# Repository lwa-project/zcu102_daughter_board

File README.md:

ZCU102 Daughter Board
=====================
This repo contains the build files for the daughter board needed to connect
the LWA digitizers to a ZCU102 dev. board.

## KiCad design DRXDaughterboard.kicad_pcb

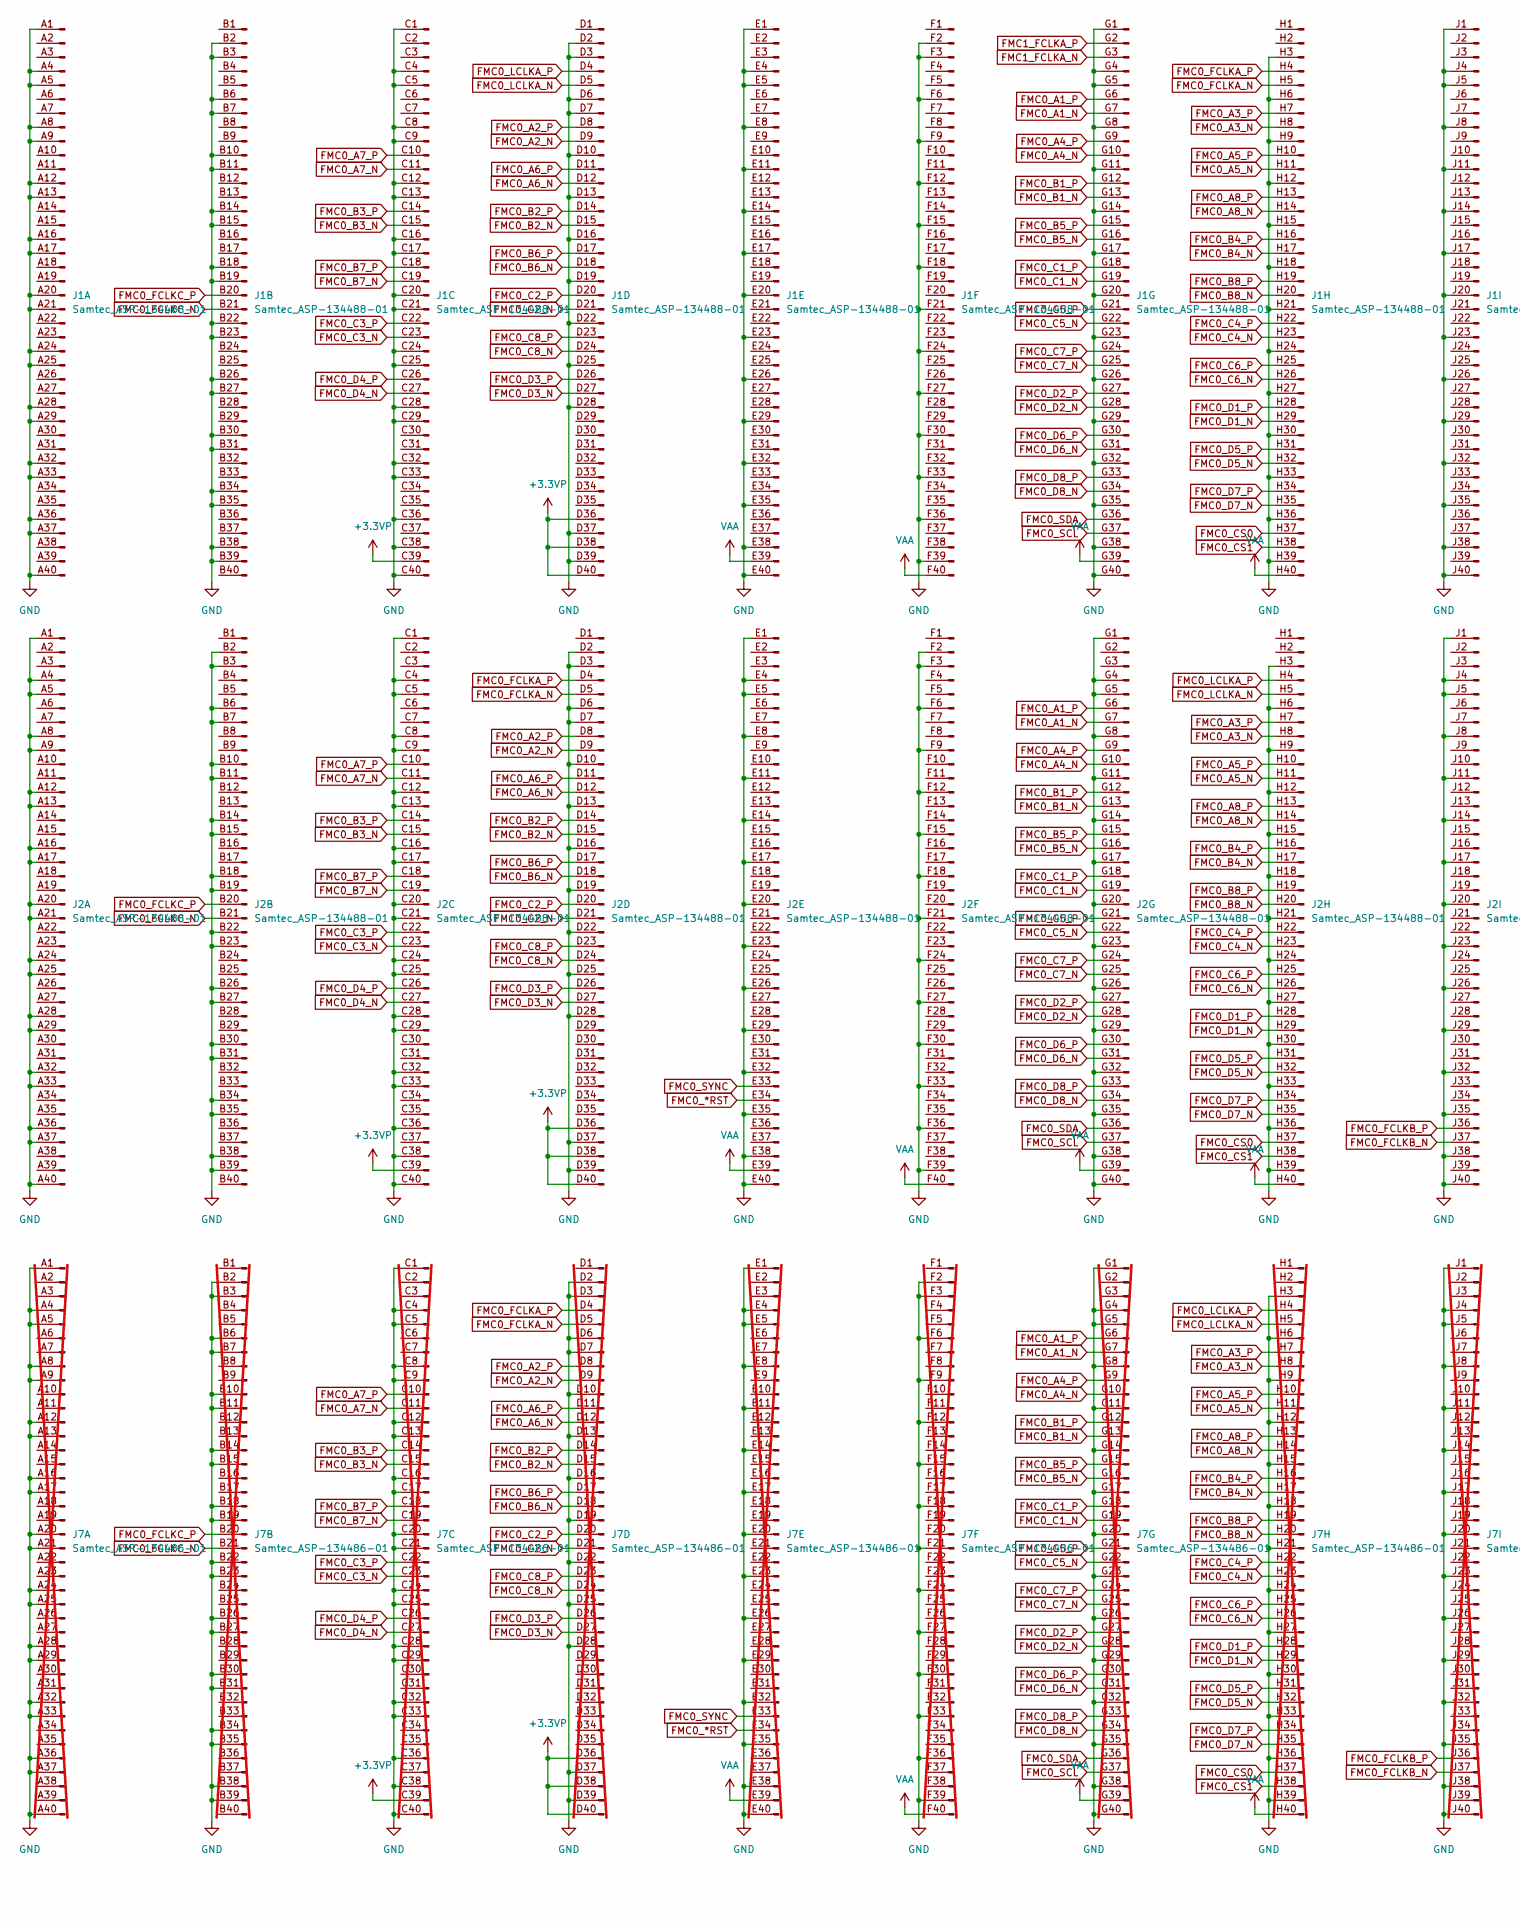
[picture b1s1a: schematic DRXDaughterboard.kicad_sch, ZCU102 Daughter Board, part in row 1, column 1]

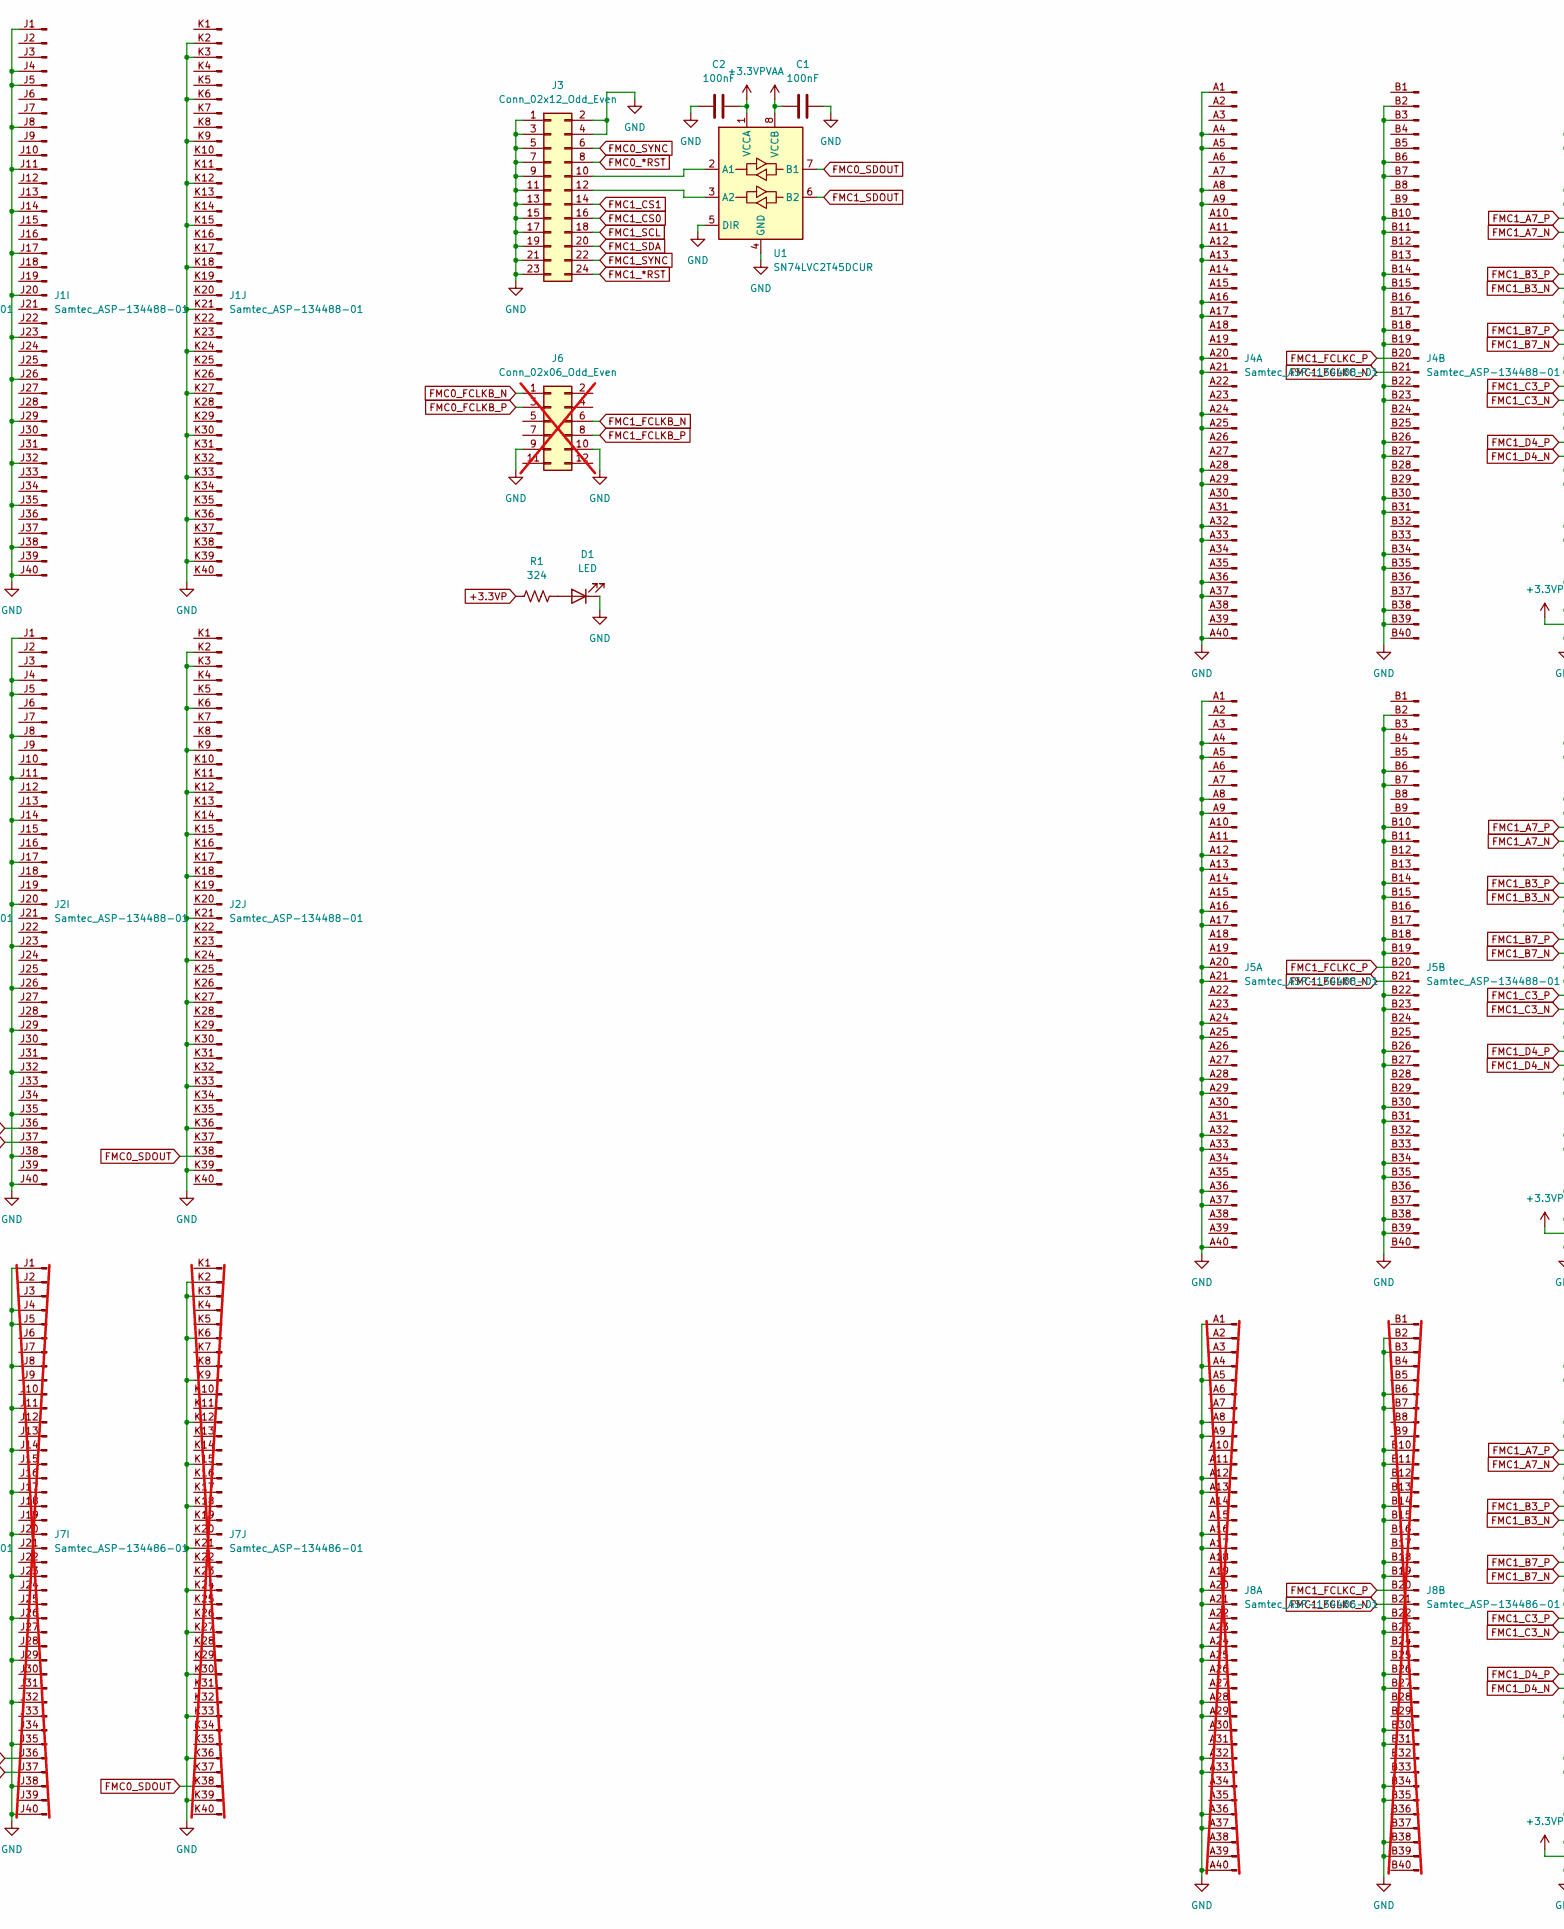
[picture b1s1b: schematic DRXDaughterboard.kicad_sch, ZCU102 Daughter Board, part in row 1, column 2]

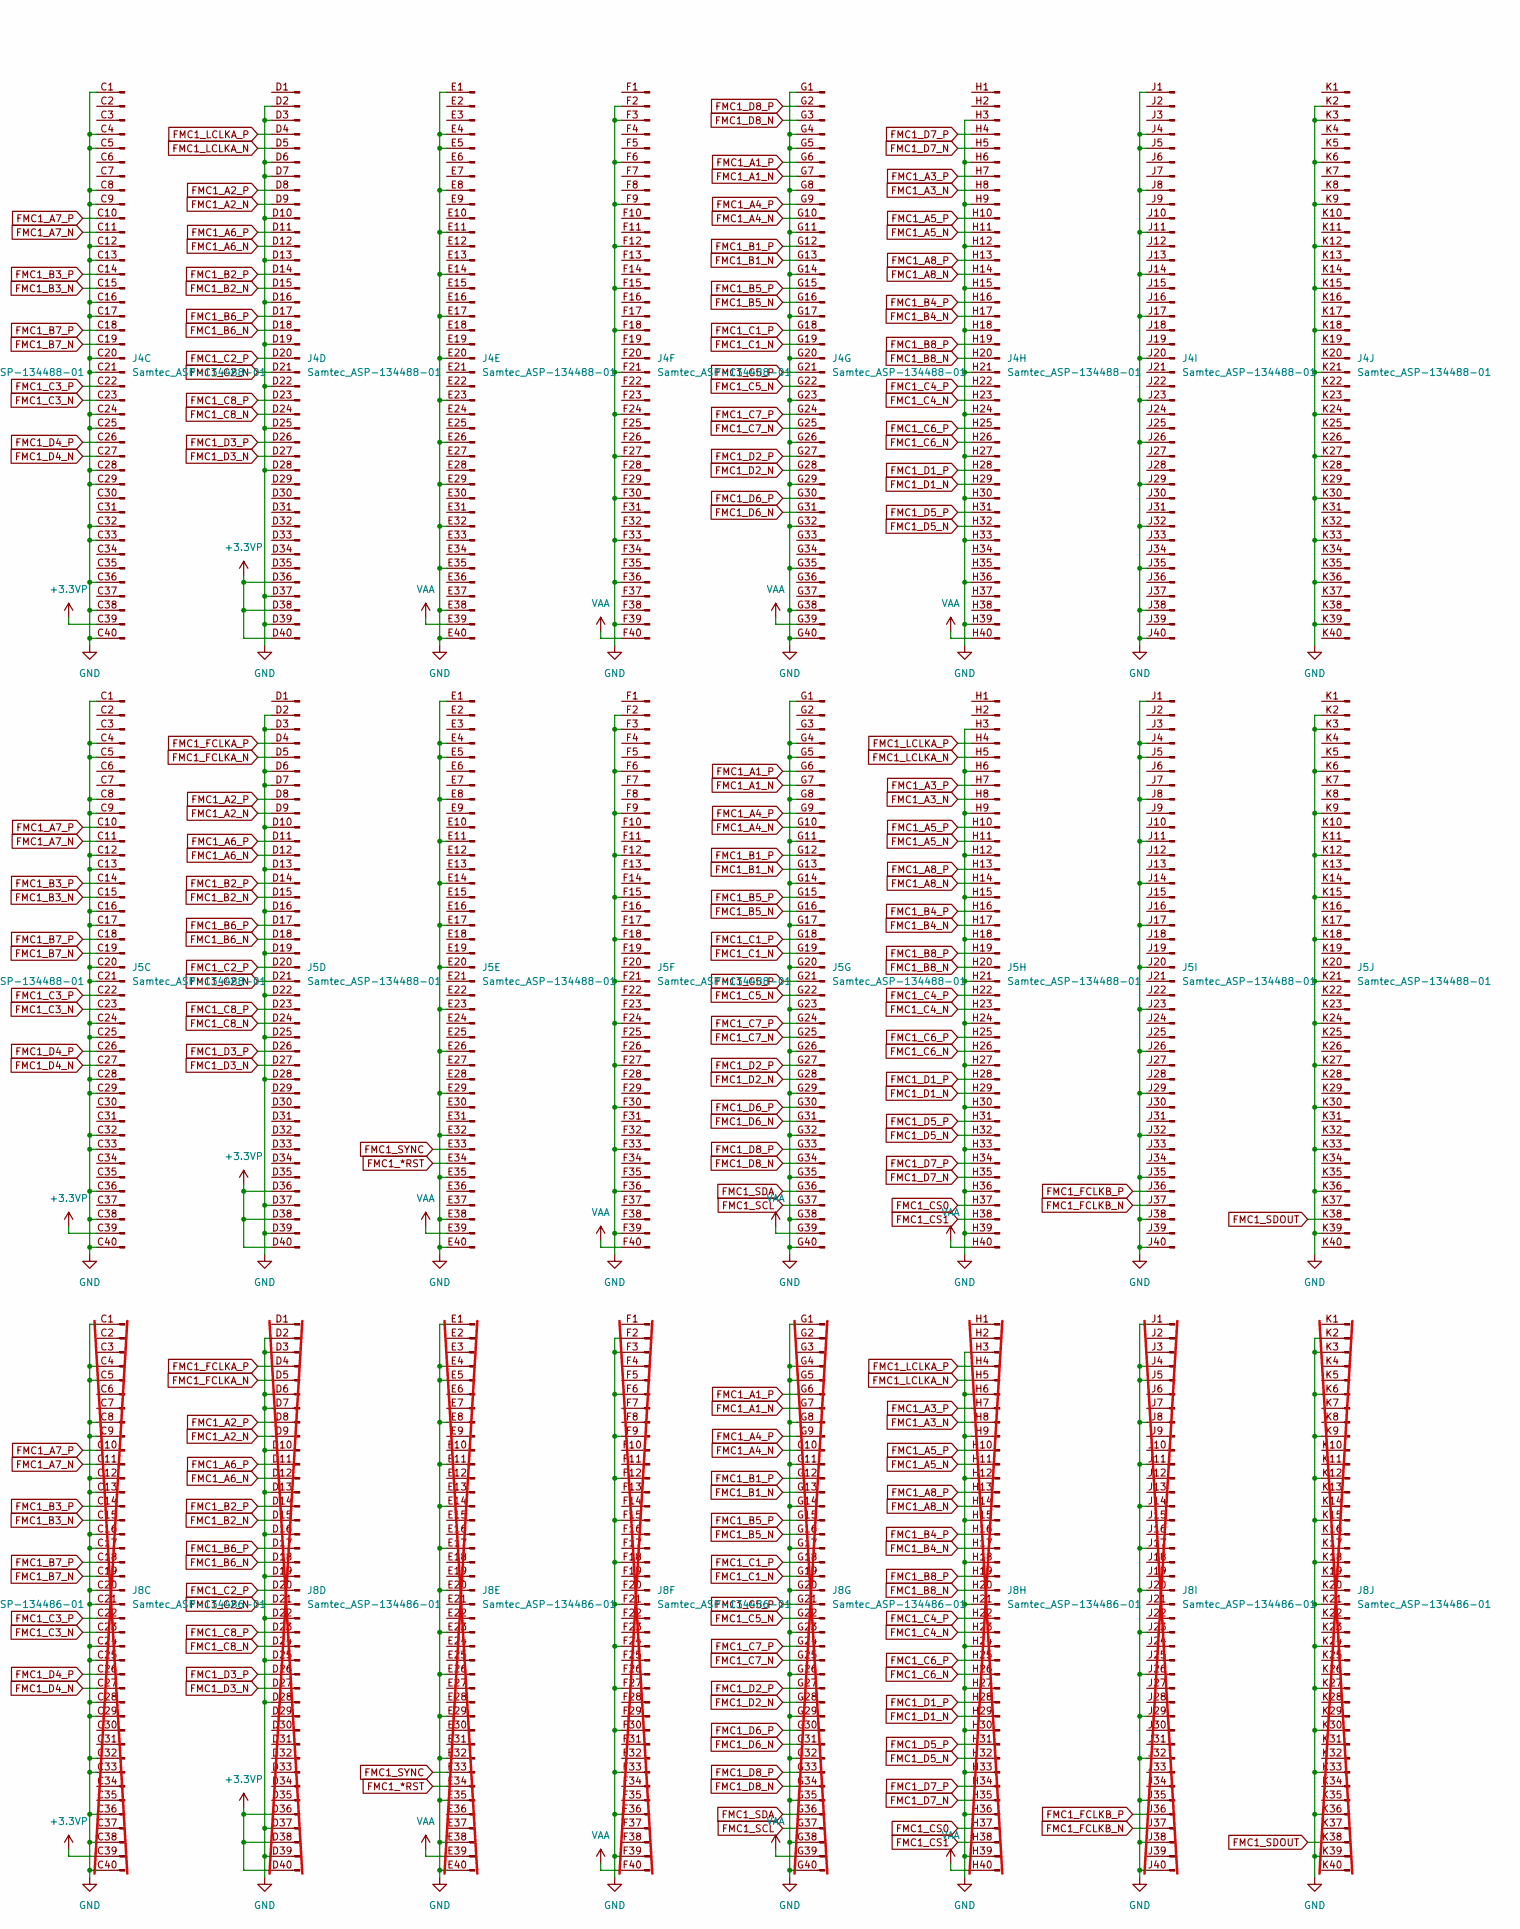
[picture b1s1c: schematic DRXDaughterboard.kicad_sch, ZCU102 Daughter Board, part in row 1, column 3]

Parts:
C1, C2: 100nF; C_1206_3216Metric_Pad1.33x1.80mm_HandSolder
D1: LED; LED_1206_3216Metric_Pad1.42x1.75mm_HandSolder
J1, J2, J4, J5: Samtec_ASP-134488-01; ASP-134488-01
J3: Conn_02x12_Odd_Even; IDC-Header_2x12_P2.54mm_Latch_Vertical
J6: Conn_02x06_Odd_Even; IDC-Header_2x06_P2.54mm_Vertical; not fitted
J7, J8: Samtec_ASP-134486-01; Samtec_FMC_ASP-134486-01_10x40_P1.27mm_Vertical; not fitted
R1: 324; R_0805_2012Metric_Pad1.20x1.40mm_HandSolder
U1: SN74LVC2T45DCUR; VSSOP-8_2.4x2.1mm_P0.5mm

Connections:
+3.3VP: C2.2, J1.C39 (Pin_39), J1.D36 (Pin_36), J1.D38 (Pin_38), J1.D40 (Pin_40), J2.C39 (Pin_39), J2.D36 (Pin_36), J2.D38 (Pin_38), J2.D40 (Pin_40), J4.C39 (Pin_39), J4.D36 (Pin_36), J4.D38 (Pin_38), J4.D40 (Pin_40), J5.C39 (Pin_39), J5.D36 (Pin_36), J5.D38 (Pin_38), J5.D40 (Pin_40), J7.C39 (Pin_39), J7.D36 (Pin_36), J7.D38 (Pin_38), J7.D40 (Pin_40), J8.C39 (Pin_39), J8.D36 (Pin_36), J8.D38 (Pin_38), J8.D40 (Pin_40), R1.1, U1.1 (VCCA)
FMC0_*RST: J2.E34 (Pin_34), J3.8, J7.E34 (Pin_34)
FMC0_A1_N: J1.G7 (Pin_7), J2.G7 (Pin_7), J7.G7 (Pin_7)
FMC0_A1_P: J1.G6 (Pin_6), J2.G6 (Pin_6), J7.G6 (Pin_6)
FMC0_A2_N: J1.D9 (Pin_9), J2.D9 (Pin_9), J7.D9 (Pin_9)
FMC0_A2_P: J1.D8 (Pin_8), J2.D8 (Pin_8), J7.D8 (Pin_8)
FMC0_A3_N: J1.H8 (Pin_8), J2.H8 (Pin_8), J7.H8 (Pin_8)
FMC0_A3_P: J1.H7 (Pin_7), J2.H7 (Pin_7), J7.H7 (Pin_7)
FMC0_A4_N: J1.G10 (Pin_10), J2.G10 (Pin_10), J7.G10 (Pin_10)
FMC0_A4_P: J1.G9 (Pin_9), J2.G9 (Pin_9), J7.G9 (Pin_9)
FMC0_A5_N: J1.H11 (Pin_11), J2.H11 (Pin_11), J7.H11 (Pin_11)
FMC0_A5_P: J1.H10 (Pin_10), J2.H10 (Pin_10), J7.H10 (Pin_10)
FMC0_A6_N: J1.D12 (Pin_12), J2.D12 (Pin_12), J7.D12 (Pin_12)
FMC0_A6_P: J1.D11 (Pin_11), J2.D11 (Pin_11), J7.D11 (Pin_11)
FMC0_A7_N: J1.C11 (Pin_11), J2.C11 (Pin_11), J7.C11 (Pin_11)
FMC0_A7_P: J1.C10 (Pin_10), J2.C10 (Pin_10), J7.C10 (Pin_10)
FMC0_A8_N: J1.H14 (Pin_14), J2.H14 (Pin_14), J7.H14 (Pin_14)
FMC0_A8_P: J1.H13 (Pin_13), J2.H13 (Pin_13), J7.H13 (Pin_13)
FMC0_B1_N: J1.G13 (Pin_13), J2.G13 (Pin_13), J7.G13 (Pin_13)
FMC0_B1_P: J1.G12 (Pin_12), J2.G12 (Pin_12), J7.G12 (Pin_12)
FMC0_B2_N: J1.D15 (Pin_15), J2.D15 (Pin_15), J7.D15 (Pin_15)
FMC0_B2_P: J1.D14 (Pin_14), J2.D14 (Pin_14), J7.D14 (Pin_14)
FMC0_B3_N: J1.C15 (Pin_15), J2.C15 (Pin_15), J7.C15 (Pin_15)
FMC0_B3_P: J1.C14 (Pin_14), J2.C14 (Pin_14), J7.C14 (Pin_14)
FMC0_B4_N: J1.H17 (Pin_17), J2.H17 (Pin_17), J7.H17 (Pin_17)
FMC0_B4_P: J1.H16 (Pin_16), J2.H16 (Pin_16), J7.H16 (Pin_16)
FMC0_B5_N: J1.G16 (Pin_16), J2.G16 (Pin_16), J7.G16 (Pin_16)
FMC0_B5_P: J1.G15 (Pin_15), J2.G15 (Pin_15), J7.G15 (Pin_15)
FMC0_B6_N: J1.D18 (Pin_18), J2.D18 (Pin_18), J7.D18 (Pin_18)
FMC0_B6_P: J1.D17 (Pin_17), J2.D17 (Pin_17), J7.D17 (Pin_17)
FMC0_B7_N: J1.C19 (Pin_19), J2.C19 (Pin_19), J7.C19 (Pin_19)
FMC0_B7_P: J1.C18 (Pin_18), J2.C18 (Pin_18), J7.C18 (Pin_18)
FMC0_B8_N: J1.H20 (Pin_20), J2.H20 (Pin_20), J7.H20 (Pin_20)
FMC0_B8_P: J1.H19 (Pin_19), J2.H19 (Pin_19), J7.H19 (Pin_19)
FMC0_C1_N: J1.G19 (Pin_19), J2.G19 (Pin_19), J7.G19 (Pin_19)
FMC0_C1_P: J1.G18 (Pin_18), J2.G18 (Pin_18), J7.G18 (Pin_18)
FMC0_C2_N: J1.D21 (Pin_21), J2.D21 (Pin_21), J7.D21 (Pin_21)
FMC0_C2_P: J1.D20 (Pin_20), J2.D20 (Pin_20), J7.D20 (Pin_20)
FMC0_C3_N: J1.C23 (Pin_23), J2.C23 (Pin_23), J7.C23 (Pin_23)
FMC0_C3_P: J1.C22 (Pin_22), J2.C22 (Pin_22), J7.C22 (Pin_22)
FMC0_C4_N: J1.H23 (Pin_23), J2.H23 (Pin_23), J7.H23 (Pin_23)
FMC0_C4_P: J1.H22 (Pin_22), J2.H22 (Pin_22), J7.H22 (Pin_22)
FMC0_C5_N: J1.G22 (Pin_22), J2.G22 (Pin_22), J7.G22 (Pin_22)
FMC0_C5_P: J1.G21 (Pin_21), J2.G21 (Pin_21), J7.G21 (Pin_21)
FMC0_C6_N: J1.H26 (Pin_26), J2.H26 (Pin_26), J7.H26 (Pin_26)
FMC0_C6_P: J1.H25 (Pin_25), J2.H25 (Pin_25), J7.H25 (Pin_25)
FMC0_C7_N: J1.G25 (Pin_25), J2.G25 (Pin_25), J7.G25 (Pin_25)
FMC0_C7_P: J1.G24 (Pin_24), J2.G24 (Pin_24), J7.G24 (Pin_24)
FMC0_C8_N: J1.D24 (Pin_24), J2.D24 (Pin_24), J7.D24 (Pin_24)
FMC0_C8_P: J1.D23 (Pin_23), J2.D23 (Pin_23), J7.D23 (Pin_23)
FMC0_CS0: J1.H37 (Pin_37), J2.H37 (Pin_37), J7.H37 (Pin_37)
FMC0_CS1: J1.H38 (Pin_38), J2.H38 (Pin_38), J7.H38 (Pin_38)
FMC0_D1_N: J1.H29 (Pin_29), J2.H29 (Pin_29), J7.H29 (Pin_29)
FMC0_D1_P: J1.H28 (Pin_28), J2.H28 (Pin_28), J7.H28 (Pin_28)
FMC0_D2_N: J1.G28 (Pin_28), J2.G28 (Pin_28), J7.G28 (Pin_28)
FMC0_D2_P: J1.G27 (Pin_27), J2.G27 (Pin_27), J7.G27 (Pin_27)
FMC0_D3_N: J1.D27 (Pin_27), J2.D27 (Pin_27), J7.D27 (Pin_27)
FMC0_D3_P: J1.D26 (Pin_26), J2.D26 (Pin_26), J7.D26 (Pin_26)
FMC0_D4_N: J1.C27 (Pin_27), J2.C27 (Pin_27), J7.C27 (Pin_27)
FMC0_D4_P: J1.C26 (Pin_26), J2.C26 (Pin_26), J7.C26 (Pin_26)
FMC0_D5_N: J1.H32 (Pin_32), J2.H32 (Pin_32), J7.H32 (Pin_32)
FMC0_D5_P: J1.H31 (Pin_31), J2.H31 (Pin_31), J7.H31 (Pin_31)
FMC0_D6_N: J1.G31 (Pin_31), J2.G31 (Pin_31), J7.G31 (Pin_31)
FMC0_D6_P: J1.G30 (Pin_30), J2.G30 (Pin_30), J7.G30 (Pin_30)
FMC0_D7_N: J1.H35 (Pin_35), J2.H35 (Pin_35), J7.H35 (Pin_35)
FMC0_D7_P: J1.H34 (Pin_34), J2.H34 (Pin_34), J7.H34 (Pin_34)
FMC0_D8_N: J1.G34 (Pin_34), J2.G34 (Pin_34), J7.G34 (Pin_34)
FMC0_D8_P: J1.G33 (Pin_33), J2.G33 (Pin_33), J7.G33 (Pin_33)
FMC0_FCLKA_N: J1.H5 (Pin_5), J2.D5 (Pin_5), J7.D5 (Pin_5)
FMC0_FCLKA_P: J1.H4 (Pin_4), J2.D4 (Pin_4), J7.D4 (Pin_4)
FMC0_FCLKB_N: J2.J37 (Pin_37), J6.1, J7.J37 (Pin_37)
FMC0_FCLKB_P: J2.J36 (Pin_36), J6.3, J7.J36 (Pin_36)
FMC0_FCLKC_N: J1.B21 (Pin_21), J2.B21 (Pin_21), J7.B21 (Pin_21)
FMC0_FCLKC_P: J1.B20 (Pin_20), J2.B20 (Pin_20), J7.B20 (Pin_20)
FMC0_LCLKA_N: J1.D5 (Pin_5), J2.H5 (Pin_5), J7.H5 (Pin_5)
FMC0_LCLKA_P: J1.D4 (Pin_4), J2.H4 (Pin_4), J7.H4 (Pin_4)
FMC0_SCL: J1.G37 (Pin_37), J2.G37 (Pin_37), J7.G37 (Pin_37)
FMC0_SDA: J1.G36 (Pin_36), J2.G36 (Pin_36), J7.G36 (Pin_36)
FMC0_SDOUT: J2.K38 (Pin_38), J7.K38 (Pin_38), U1.7 (B1)
FMC0_SYNC: J2.E33 (Pin_33), J3.6, J7.E33 (Pin_33)
FMC1_*RST: J3.24, J5.E34 (Pin_34), J8.E34 (Pin_34)
FMC1_A1_N: J4.G7 (Pin_7), J5.G7 (Pin_7), J8.G7 (Pin_7)
FMC1_A1_P: J4.G6 (Pin_6), J5.G6 (Pin_6), J8.G6 (Pin_6)
FMC1_A2_N: J4.D9 (Pin_9), J5.D9 (Pin_9), J8.D9 (Pin_9)
FMC1_A2_P: J4.D8 (Pin_8), J5.D8 (Pin_8), J8.D8 (Pin_8)
FMC1_A3_N: J4.H8 (Pin_8), J5.H8 (Pin_8), J8.H8 (Pin_8)
FMC1_A3_P: J4.H7 (Pin_7), J5.H7 (Pin_7), J8.H7 (Pin_7)
FMC1_A4_N: J4.G10 (Pin_10), J5.G10 (Pin_10), J8.G10 (Pin_10)
FMC1_A4_P: J4.G9 (Pin_9), J5.G9 (Pin_9), J8.G9 (Pin_9)
FMC1_A5_N: J4.H11 (Pin_11), J5.H11 (Pin_11), J8.H11 (Pin_11)
FMC1_A5_P: J4.H10 (Pin_10), J5.H10 (Pin_10), J8.H10 (Pin_10)
FMC1_A6_N: J4.D12 (Pin_12), J5.D12 (Pin_12), J8.D12 (Pin_12)
FMC1_A6_P: J4.D11 (Pin_11), J5.D11 (Pin_11), J8.D11 (Pin_11)
FMC1_A7_N: J4.C11 (Pin_11), J5.C11 (Pin_11), J8.C11 (Pin_11)
FMC1_A7_P: J4.C10 (Pin_10), J5.C10 (Pin_10), J8.C10 (Pin_10)
FMC1_A8_N: J4.H14 (Pin_14), J5.H14 (Pin_14), J8.H14 (Pin_14)
FMC1_A8_P: J4.H13 (Pin_13), J5.H13 (Pin_13), J8.H13 (Pin_13)
FMC1_B1_N: J4.G13 (Pin_13), J5.G13 (Pin_13), J8.G13 (Pin_13)
FMC1_B1_P: J4.G12 (Pin_12), J5.G12 (Pin_12), J8.G12 (Pin_12)
FMC1_B2_N: J4.D15 (Pin_15), J5.D15 (Pin_15), J8.D15 (Pin_15)
FMC1_B2_P: J4.D14 (Pin_14), J5.D14 (Pin_14), J8.D14 (Pin_14)
FMC1_B3_N: J4.C15 (Pin_15), J5.C15 (Pin_15), J8.C15 (Pin_15)
FMC1_B3_P: J4.C14 (Pin_14), J5.C14 (Pin_14), J8.C14 (Pin_14)
FMC1_B4_N: J4.H17 (Pin_17), J5.H17 (Pin_17), J8.H17 (Pin_17)
FMC1_B4_P: J4.H16 (Pin_16), J5.H16 (Pin_16), J8.H16 (Pin_16)
FMC1_B5_N: J4.G16 (Pin_16), J5.G16 (Pin_16), J8.G16 (Pin_16)
FMC1_B5_P: J4.G15 (Pin_15), J5.G15 (Pin_15), J8.G15 (Pin_15)
FMC1_B6_N: J4.D18 (Pin_18), J5.D18 (Pin_18), J8.D18 (Pin_18)
FMC1_B6_P: J4.D17 (Pin_17), J5.D17 (Pin_17), J8.D17 (Pin_17)
FMC1_B7_N: J4.C19 (Pin_19), J5.C19 (Pin_19), J8.C19 (Pin_19)
FMC1_B7_P: J4.C18 (Pin_18), J5.C18 (Pin_18), J8.C18 (Pin_18)
FMC1_B8_N: J4.H20 (Pin_20), J5.H20 (Pin_20), J8.H20 (Pin_20)
FMC1_B8_P: J4.H19 (Pin_19), J5.H19 (Pin_19), J8.H19 (Pin_19)
FMC1_C1_N: J4.G19 (Pin_19), J5.G19 (Pin_19), J8.G19 (Pin_19)
FMC1_C1_P: J4.G18 (Pin_18), J5.G18 (Pin_18), J8.G18 (Pin_18)
FMC1_C2_N: J4.D21 (Pin_21), J5.D21 (Pin_21), J8.D21 (Pin_21)
FMC1_C2_P: J4.D20 (Pin_20), J5.D20 (Pin_20), J8.D20 (Pin_20)
FMC1_C3_N: J4.C23 (Pin_23), J5.C23 (Pin_23), J8.C23 (Pin_23)
FMC1_C3_P: J4.C22 (Pin_22), J5.C22 (Pin_22), J8.C22 (Pin_22)
FMC1_C4_N: J4.H23 (Pin_23), J5.H23 (Pin_23), J8.H23 (Pin_23)
FMC1_C4_P: J4.H22 (Pin_22), J5.H22 (Pin_22), J8.H22 (Pin_22)
FMC1_C5_N: J4.G22 (Pin_22), J5.G22 (Pin_22), J8.G22 (Pin_22)
FMC1_C5_P: J4.G21 (Pin_21), J5.G21 (Pin_21), J8.G21 (Pin_21)
FMC1_C6_N: J4.H26 (Pin_26), J5.H26 (Pin_26), J8.H26 (Pin_26)
FMC1_C6_P: J4.H25 (Pin_25), J5.H25 (Pin_25), J8.H25 (Pin_25)
FMC1_C7_N: J4.G25 (Pin_25), J5.G25 (Pin_25), J8.G25 (Pin_25)
FMC1_C7_P: J4.G24 (Pin_24), J5.G24 (Pin_24), J8.G24 (Pin_24)
FMC1_C8_N: J4.D24 (Pin_24), J5.D24 (Pin_24), J8.D24 (Pin_24)
FMC1_C8_P: J4.D23 (Pin_23), J5.D23 (Pin_23), J8.D23 (Pin_23)
FMC1_CS0: J3.16, J5.H37 (Pin_37), J8.H37 (Pin_37)
FMC1_CS1: J3.14, J5.H38 (Pin_38), J8.H38 (Pin_38)
FMC1_D1_N: J4.H29 (Pin_29), J5.H29 (Pin_29), J8.H29 (Pin_29)
FMC1_D1_P: J4.H28 (Pin_28), J5.H28 (Pin_28), J8.H28 (Pin_28)
FMC1_D2_N: J4.G28 (Pin_28), J5.G28 (Pin_28), J8.G28 (Pin_28)
FMC1_D2_P: J4.G27 (Pin_27), J5.G27 (Pin_27), J8.G27 (Pin_27)
FMC1_D3_N: J4.D27 (Pin_27), J5.D27 (Pin_27), J8.D27 (Pin_27)
FMC1_D3_P: J4.D26 (Pin_26), J5.D26 (Pin_26), J8.D26 (Pin_26)
FMC1_D4_N: J4.C27 (Pin_27), J5.C27 (Pin_27), J8.C27 (Pin_27)
FMC1_D4_P: J4.C26 (Pin_26), J5.C26 (Pin_26), J8.C26 (Pin_26)
FMC1_D5_N: J4.H32 (Pin_32), J5.H32 (Pin_32), J8.H32 (Pin_32)
FMC1_D5_P: J4.H31 (Pin_31), J5.H31 (Pin_31), J8.H31 (Pin_31)
FMC1_D6_N: J4.G31 (Pin_31), J5.G31 (Pin_31), J8.G31 (Pin_31)
FMC1_D6_P: J4.G30 (Pin_30), J5.G30 (Pin_30), J8.G30 (Pin_30)
FMC1_D7_N: J4.H5 (Pin_5), J5.H35 (Pin_35), J8.H35 (Pin_35)
FMC1_D7_P: J4.H4 (Pin_4), J5.H34 (Pin_34), J8.H34 (Pin_34)
FMC1_D8_N: J4.G3 (Pin_3), J5.G34 (Pin_34), J8.G34 (Pin_34)
FMC1_D8_P: J4.G2 (Pin_2), J5.G33 (Pin_33), J8.G33 (Pin_33)
FMC1_FCLKA_N: J1.G3 (Pin_3), J5.D5 (Pin_5), J8.D5 (Pin_5)
FMC1_FCLKA_P: J1.G2 (Pin_2), J5.D4 (Pin_4), J8.D4 (Pin_4)
FMC1_FCLKB_N: J5.J37 (Pin_37), J6.6, J8.J37 (Pin_37)
FMC1_FCLKB_P: J5.J36 (Pin_36), J6.8, J8.J36 (Pin_36)
FMC1_FCLKC_N: J4.B21 (Pin_21), J5.B21 (Pin_21), J8.B21 (Pin_21)
FMC1_FCLKC_P: J4.B20 (Pin_20), J5.B20 (Pin_20), J8.B20 (Pin_20)
FMC1_LCLKA_N: J4.D5 (Pin_5), J5.H5 (Pin_5), J8.H5 (Pin_5)
FMC1_LCLKA_P: J4.D4 (Pin_4), J5.H4 (Pin_4), J8.H4 (Pin_4)
FMC1_SCL: J3.18, J5.G37 (Pin_37), J8.G37 (Pin_37)
FMC1_SDA: J3.20, J5.G36 (Pin_36), J8.G36 (Pin_36)
FMC1_SDOUT: J5.K38 (Pin_38), J8.K38 (Pin_38), U1.6 (B2)
FMC1_SYNC: J3.22, J5.E33 (Pin_33), J8.E33 (Pin_33)
GND: C1.2, C2.1, D1.1 (K), J1.A1 (Pin_1), J1.A4 (Pin_4), J1.A5 (Pin_5), J1.A8 (Pin_8), J1.A9 (Pin_9), J1.A12 (Pin_12), J1.A13 (Pin_13), J1.A16 (Pin_16), J1.A17 (Pin_17), J1.A20 (Pin_20), J1.A21 (Pin_21), J1.A24 (Pin_24), J1.A25 (Pin_25), J1.A28 (Pin_28), J1.A29 (Pin_29), J1.A32 (Pin_32), J1.A33 (Pin_33), J1.A36 (Pin_36), J1.A37 (Pin_37), J1.A40 (Pin_40), J1.B2 (Pin_2), J1.B3 (Pin_3), J1.B6 (Pin_6), J1.B7 (Pin_7), J1.B10 (Pin_10), J1.B11 (Pin_11), J1.B14 (Pin_14), J1.B15 (Pin_15), J1.B18 (Pin_18), J1.B19 (Pin_19), J1.B22 (Pin_22), J1.B23 (Pin_23), J1.B26 (Pin_26), J1.B27 (Pin_27), J1.B30 (Pin_30), J1.B31 (Pin_31), J1.B34 (Pin_34), J1.B35 (Pin_35), J1.B38 (Pin_38), J1.B39 (Pin_39), J1.C1 (Pin_1), J1.C4 (Pin_4), J1.C5 (Pin_5), J1.C8 (Pin_8), J1.C9 (Pin_9), J1.C12 (Pin_12), J1.C13 (Pin_13), J1.C16 (Pin_16), J1.C17 (Pin_17), J1.C20 (Pin_20), J1.C21 (Pin_21), J1.C24 (Pin_24), J1.C25 (Pin_25), J1.C28 (Pin_28), J1.C29 (Pin_29), J1.C32 (Pin_32), J1.C33 (Pin_33), J1.C36 (Pin_36), J1.C38 (Pin_38), J1.C40 (Pin_40), J1.D2 (Pin_2), J1.D3 (Pin_3), J1.D6 (Pin_6), J1.D7 (Pin_7), J1.D10 (Pin_10), J1.D13 (Pin_13), J1.D16 (Pin_16), J1.D19 (Pin_19), J1.D22 (Pin_22), J1.D25 (Pin_25), J1.D28 (Pin_28), J1.D37 (Pin_37), J1.D39 (Pin_39), J1.E1 (Pin_1), J1.E4 (Pin_4), J1.E5 (Pin_5), J1.E8 (Pin_8), J1.E11 (Pin_11), J1.E14 (Pin_14), J1.E17 (Pin_17), J1.E20 (Pin_20), J1.E23 (Pin_23), J1.E26 (Pin_26), J1.E29 (Pin_29), J1.E32 (Pin_32), J1.E35 (Pin_35), J1.E38 (Pin_38), J1.E40 (Pin_40), J1.F2 (Pin_2), J1.F3 (Pin_3), J1.F6 (Pin_6), J1.F9 (Pin_9), J1.F12 (Pin_12), J1.F15 (Pin_15), J1.F18 (Pin_18), J1.F21 (Pin_21), J1.F24 (Pin_24), J1.F27 (Pin_27), J1.F30 (Pin_30), J1.F33 (Pin_33), J1.F36 (Pin_36), J1.F39 (Pin_39), J1.G1 (Pin_1), J1.G4 (Pin_4), J1.G5 (Pin_5), J1.G8 (Pin_8), J1.G11 (Pin_11), J1.G14 (Pin_14), J1.G17 (Pin_17), J1.G20 (Pin_20), J1.G23 (Pin_23), J1.G26 (Pin_26), J1.G29 (Pin_29), J1.G32 (Pin_32), J1.G35 (Pin_35), J1.G38 (Pin_38), J1.G40 (Pin_40), J1.H3 (Pin_3), J1.H6 (Pin_6), J1.H9 (Pin_9), J1.H12 (Pin_12), J1.H15 (Pin_15), J1.H18 (Pin_18), J1.H21 (Pin_21), J1.H24 (Pin_24), J1.H27 (Pin_27), J1.H30 (Pin_30), J1.H33 (Pin_33), J1.H36 (Pin_36), J1.H39 (Pin_39), J1.J1 (Pin_1), J1.J4 (Pin_4), J1.J5 (Pin_5), J1.J8 (Pin_8), J1.J11 (Pin_11), J1.J14 (Pin_14), J1.J17 (Pin_17), J1.J20 (Pin_20), J1.J23 (Pin_23), J1.J26 (Pin_26), J1.J29 (Pin_29), J1.J32 (Pin_32), J1.J35 (Pin_35), J1.J38 (Pin_38), J1.J40 (Pin_40), J1.K2 (Pin_2), J1.K3 (Pin_3), J1.K6 (Pin_6), J1.K9 (Pin_9), J1.K12 (Pin_12), J1.K15 (Pin_15), J1.K18 (Pin_18), J1.K21 (Pin_21), J1.K24 (Pin_24), J1.K27 (Pin_27), J1.K30 (Pin_30), J1.K33 (Pin_33), J1.K36 (Pin_36), J1.K39 (Pin_39), J2.A1 (Pin_1), J2.A4 (Pin_4), J2.A5 (Pin_5), J2.A8 (Pin_8), J2.A9 (Pin_9), J2.A12 (Pin_12), J2.A13 (Pin_13), J2.A16 (Pin_16), J2.A17 (Pin_17), J2.A20 (Pin_20), J2.A21 (Pin_21), J2.A24 (Pin_24), J2.A25 (Pin_25), J2.A28 (Pin_28), J2.A29 (Pin_29), J2.A32 (Pin_32), J2.A33 (Pin_33), J2.A36 (Pin_36), J2.A37 (Pin_37), J2.A40 (Pin_40), J2.B2 (Pin_2), J2.B3 (Pin_3), J2.B6 (Pin_6), J2.B7 (Pin_7), J2.B10 (Pin_10), J2.B11 (Pin_11), J2.B14 (Pin_14), J2.B15 (Pin_15), J2.B18 (Pin_18), J2.B19 (Pin_19), J2.B22 (Pin_22), J2.B23 (Pin_23), J2.B26 (Pin_26), J2.B27 (Pin_27), J2.B30 (Pin_30), J2.B31 (Pin_31), J2.B34 (Pin_34), J2.B35 (Pin_35), J2.B38 (Pin_38), J2.B39 (Pin_39), J2.C1 (Pin_1), J2.C4 (Pin_4), J2.C5 (Pin_5), J2.C8 (Pin_8), J2.C9 (Pin_9), J2.C12 (Pin_12), J2.C13 (Pin_13), J2.C16 (Pin_16), J2.C17 (Pin_17), J2.C20 (Pin_20), J2.C21 (Pin_21), J2.C24 (Pin_24), J2.C25 (Pin_25), J2.C28 (Pin_28), J2.C29 (Pin_29), J2.C32 (Pin_32), J2.C33 (Pin_33), J2.C36 (Pin_36), J2.C38 (Pin_38), J2.C40 (Pin_40), J2.D2 (Pin_2), J2.D3 (Pin_3), J2.D6 (Pin_6), J2.D7 (Pin_7), J2.D10 (Pin_10), J2.D13 (Pin_13), J2.D16 (Pin_16), J2.D19 (Pin_19), J2.D22 (Pin_22), J2.D25 (Pin_25), J2.D28 (Pin_28), J2.D37 (Pin_37), J2.D39 (Pin_39), J2.E1 (Pin_1), J2.E4 (Pin_4), J2.E5 (Pin_5), J2.E8 (Pin_8), J2.E11 (Pin_11), J2.E14 (Pin_14), J2.E17 (Pin_17), J2.E20 (Pin_20), J2.E23 (Pin_23), J2.E26 (Pin_26), J2.E29 (Pin_29), J2.E32 (Pin_32), J2.E35 (Pin_35), J2.E38 (Pin_38), J2.E40 (Pin_40), J2.F2 (Pin_2), J2.F3 (Pin_3), J2.F6 (Pin_6), J2.F9 (Pin_9), J2.F12 (Pin_12), J2.F15 (Pin_15), J2.F18 (Pin_18), J2.F21 (Pin_21), J2.F24 (Pin_24), J2.F27 (Pin_27), J2.F30 (Pin_30), J2.F33 (Pin_33), J2.F36 (Pin_36), J2.F39 (Pin_39), J2.G1 (Pin_1), J2.G4 (Pin_4), J2.G5 (Pin_5), J2.G8 (Pin_8), J2.G11 (Pin_11), J2.G14 (Pin_14), J2.G17 (Pin_17), J2.G20 (Pin_20), J2.G23 (Pin_23), J2.G26 (Pin_26), J2.G29 (Pin_29), J2.G32 (Pin_32), J2.G35 (Pin_35), J2.G38 (Pin_38), J2.G40 (Pin_40), J2.H3 (Pin_3), J2.H6 (Pin_6), J2.H9 (Pin_9), J2.H12 (Pin_12), J2.H15 (Pin_15), J2.H18 (Pin_18), J2.H21 (Pin_21), J2.H24 (Pin_24), J2.H27 (Pin_27), J2.H30 (Pin_30), J2.H33 (Pin_33), J2.H36 (Pin_36), J2.H39 (Pin_39), J2.J1 (Pin_1), J2.J4 (Pin_4), J2.J5 (Pin_5), J2.J8 (Pin_8), J2.J11 (Pin_11), J2.J14 (Pin_14), J2.J17 (Pin_17), J2.J20 (Pin_20), J2.J23 (Pin_23), J2.J26 (Pin_26), J2.J29 (Pin_29), J2.J32 (Pin_32), J2.J35 (Pin_35), J2.J38 (Pin_38), J2.J40 (Pin_40), J2.K2 (Pin_2), J2.K3 (Pin_3), J2.K6 (Pin_6), J2.K9 (Pin_9), J2.K12 (Pin_12), J2.K15 (Pin_15), J2.K18 (Pin_18), J2.K21 (Pin_21), J2.K24 (Pin_24), J2.K27 (Pin_27), J2.K30 (Pin_30), J2.K33 (Pin_33), J2.K36 (Pin_36), J2.K39 (Pin_39), J3.1, J3.2, J3.3, J3.4, J3.5, J3.7, J3.9, J3.11, J3.13, J3.15, J3.17, J3.19, J3.21, J3.23, J4.A1 (Pin_1), J4.A4 (Pin_4), J4.A5 (Pin_5), J4.A8 (Pin_8), J4.A9 (Pin_9), J4.A12 (Pin_12), J4.A13 (Pin_13), J4.A16 (Pin_16), J4.A17 (Pin_17), J4.A20 (Pin_20), J4.A21 (Pin_21), J4.A24 (Pin_24), J4.A25 (Pin_25), J4.A28 (Pin_28), J4.A29 (Pin_29), J4.A32 (Pin_32), J4.A33 (Pin_33), J4.A36 (Pin_36), J4.A37 (Pin_37), J4.A40 (Pin_40), J4.B2 (Pin_2), J4.B3 (Pin_3), J4.B6 (Pin_6), J4.B7 (Pin_7), J4.B10 (Pin_10), J4.B11 (Pin_11), J4.B14 (Pin_14), J4.B15 (Pin_15), J4.B18 (Pin_18), J4.B19 (Pin_19), J4.B22 (Pin_22), J4.B23 (Pin_23), J4.B26 (Pin_26), J4.B27 (Pin_27), J4.B30 (Pin_30), J4.B31 (Pin_31), J4.B34 (Pin_34), J4.B35 (Pin_35), J4.B38 (Pin_38), J4.B39 (Pin_39), J4.C1 (Pin_1), J4.C4 (Pin_4), J4.C5 (Pin_5), J4.C8 (Pin_8), J4.C9 (Pin_9), J4.C12 (Pin_12), J4.C13 (Pin_13), J4.C16 (Pin_16), J4.C17 (Pin_17), J4.C20 (Pin_20), J4.C21 (Pin_21), J4.C24 (Pin_24), J4.C25 (Pin_25), J4.C28 (Pin_28), J4.C29 (Pin_29), J4.C32 (Pin_32), J4.C33 (Pin_33), J4.C36 (Pin_36), J4.C38 (Pin_38), J4.C40 (Pin_40), J4.D2 (Pin_2), J4.D3 (Pin_3), J4.D6 (Pin_6), J4.D7 (Pin_7), J4.D10 (Pin_10), J4.D13 (Pin_13), J4.D16 (Pin_16), J4.D19 (Pin_19), J4.D22 (Pin_22), J4.D25 (Pin_25), J4.D28 (Pin_28), J4.D37 (Pin_37), J4.D39 (Pin_39), J4.E1 (Pin_1), J4.E4 (Pin_4), J4.E5 (Pin_5), J4.E8 (Pin_8), J4.E11 (Pin_11), J4.E14 (Pin_14), J4.E17 (Pin_17), J4.E20 (Pin_20), J4.E23 (Pin_23), J4.E26 (Pin_26), J4.E29 (Pin_29), J4.E32 (Pin_32), J4.E35 (Pin_35), J4.E38 (Pin_38), J4.E40 (Pin_40), J4.F2 (Pin_2), J4.F3 (Pin_3), J4.F6 (Pin_6), J4.F9 (Pin_9), J4.F12 (Pin_12), J4.F15 (Pin_15), J4.F18 (Pin_18), J4.F21 (Pin_21), J4.F24 (Pin_24), J4.F27 (Pin_27), J4.F30 (Pin_30), J4.F33 (Pin_33), J4.F36 (Pin_36), J4.F39 (Pin_39), J4.G1 (Pin_1), J4.G4 (Pin_4), J4.G5 (Pin_5), J4.G8 (Pin_8), J4.G11 (Pin_11), J4.G14 (Pin_14), J4.G17 (Pin_17), J4.G20 (Pin_20), J4.G23 (Pin_23), J4.G26 (Pin_26), J4.G29 (Pin_29), J4.G32 (Pin_32), J4.G35 (Pin_35), J4.G38 (Pin_38), J4.G40 (Pin_40), J4.H3 (Pin_3), J4.H6 (Pin_6), J4.H9 (Pin_9), J4.H12 (Pin_12), J4.H15 (Pin_15), J4.H18 (Pin_18), J4.H21 (Pin_21), J4.H24 (Pin_24), J4.H27 (Pin_27), J4.H30 (Pin_30), J4.H33 (Pin_33), J4.H36 (Pin_36), J4.H39 (Pin_39), J4.J1 (Pin_1), J4.J4 (Pin_4), J4.J5 (Pin_5), J4.J8 (Pin_8), J4.J11 (Pin_11), J4.J14 (Pin_14), J4.J17 (Pin_17), J4.J20 (Pin_20), J4.J23 (Pin_23), J4.J26 (Pin_26), J4.J29 (Pin_29), J4.J32 (Pin_32), J4.J35 (Pin_35), J4.J38 (Pin_38), J4.J40 (Pin_40), J4.K2 (Pin_2), J4.K3 (Pin_3), J4.K6 (Pin_6), J4.K9 (Pin_9), J4.K12 (Pin_12), J4.K15 (Pin_15), J4.K18 (Pin_18), J4.K21 (Pin_21), J4.K24 (Pin_24), J4.K27 (Pin_27), J4.K30 (Pin_30), J4.K33 (Pin_33), J4.K36 (Pin_36), J4.K39 (Pin_39), J5.A1 (Pin_1), J5.A4 (Pin_4), J5.A5 (Pin_5), J5.A8 (Pin_8), J5.A9 (Pin_9), J5.A12 (Pin_12), J5.A13 (Pin_13), J5.A16 (Pin_16), J5.A17 (Pin_17), J5.A20 (Pin_20), J5.A21 (Pin_21), J5.A24 (Pin_24), J5.A25 (Pin_25), J5.A28 (Pin_28), J5.A29 (Pin_29), J5.A32 (Pin_32), J5.A33 (Pin_33), J5.A36 (Pin_36), J5.A37 (Pin_37), J5.A40 (Pin_40), J5.B2 (Pin_2), J5.B3 (Pin_3), J5.B6 (Pin_6), J5.B7 (Pin_7), J5.B10 (Pin_10), J5.B11 (Pin_11), J5.B14 (Pin_14), J5.B15 (Pin_15), J5.B18 (Pin_18), J5.B19 (Pin_19), J5.B22 (Pin_22), J5.B23 (Pin_23), J5.B26 (Pin_26), J5.B27 (Pin_27), J5.B30 (Pin_30), J5.B31 (Pin_31), J5.B34 (Pin_34), J5.B35 (Pin_35), J5.B38 (Pin_38), J5.B39 (Pin_39), J5.C1 (Pin_1), J5.C4 (Pin_4), J5.C5 (Pin_5), J5.C8 (Pin_8), J5.C9 (Pin_9), J5.C12 (Pin_12), J5.C13 (Pin_13), J5.C16 (Pin_16), J5.C17 (Pin_17), J5.C20 (Pin_20), J5.C21 (Pin_21), J5.C24 (Pin_24), J5.C25 (Pin_25), J5.C28 (Pin_28), J5.C29 (Pin_29), J5.C32 (Pin_32), J5.C33 (Pin_33), J5.C36 (Pin_36), J5.C38 (Pin_38), J5.C40 (Pin_40), J5.D2 (Pin_2), J5.D3 (Pin_3), J5.D6 (Pin_6), J5.D7 (Pin_7), J5.D10 (Pin_10), J5.D13 (Pin_13), J5.D16 (Pin_16), J5.D19 (Pin_19), J5.D22 (Pin_22), J5.D25 (Pin_25), J5.D28 (Pin_28), J5.D37 (Pin_37), J5.D39 (Pin_39), J5.E1 (Pin_1), J5.E4 (Pin_4), J5.E5 (Pin_5), J5.E8 (Pin_8), J5.E11 (Pin_11), J5.E14 (Pin_14), J5.E17 (Pin_17), J5.E20 (Pin_20), J5.E23 (Pin_23), J5.E26 (Pin_26), J5.E29 (Pin_29), J5.E32 (Pin_32), J5.E35 (Pin_35), J5.E38 (Pin_38), J5.E40 (Pin_40), J5.F2 (Pin_2), J5.F3 (Pin_3), J5.F6 (Pin_6), J5.F9 (Pin_9), J5.F12 (Pin_12), J5.F15 (Pin_15), J5.F18 (Pin_18), J5.F21 (Pin_21), J5.F24 (Pin_24), J5.F27 (Pin_27), J5.F30 (Pin_30), J5.F33 (Pin_33), J5.F36 (Pin_36), J5.F39 (Pin_39), J5.G1 (Pin_1), J5.G4 (Pin_4), J5.G5 (Pin_5), J5.G8 (Pin_8), J5.G11 (Pin_11), J5.G14 (Pin_14), J5.G17 (Pin_17), J5.G20 (Pin_20), J5.G23 (Pin_23), J5.G26 (Pin_26), J5.G29 (Pin_29), J5.G32 (Pin_32), J5.G35 (Pin_35), J5.G38 (Pin_38), J5.G40 (Pin_40), J5.H3 (Pin_3), J5.H6 (Pin_6), J5.H9 (Pin_9), J5.H12 (Pin_12), J5.H15 (Pin_15), J5.H18 (Pin_18), J5.H21 (Pin_21), J5.H24 (Pin_24), J5.H27 (Pin_27), J5.H30 (Pin_30), J5.H33 (Pin_33), J5.H36 (Pin_36), J5.H39 (Pin_39), J5.J1 (Pin_1), J5.J4 (Pin_4), J5.J5 (Pin_5), J5.J8 (Pin_8), J5.J11 (Pin_11), J5.J14 (Pin_14), J5.J17 (Pin_17), J5.J20 (Pin_20), J5.J23 (Pin_23), J5.J26 (Pin_26), J5.J29 (Pin_29), J5.J32 (Pin_32), J5.J35 (Pin_35), J5.J38 (Pin_38), J5.J40 (Pin_40), J5.K2 (Pin_2), J5.K3 (Pin_3), J5.K6 (Pin_6), J5.K9 (Pin_9), J5.K12 (Pin_12), J5.K15 (Pin_15), J5.K18 (Pin_18), J5.K21 (Pin_21), J5.K24 (Pin_24), J5.K27 (Pin_27), J5.K30 (Pin_30), J5.K33 (Pin_33), J5.K36 (Pin_36), J5.K39 (Pin_39), J6.9, J6.10, J7.A1 (Pin_1), J7.A4 (Pin_4), J7.A5 (Pin_5), J7.A8 (Pin_8), J7.A9 (Pin_9), J7.A12 (Pin_12), J7.A13 (Pin_13), J7.A16 (Pin_16), J7.A17 (Pin_17), J7.A20 (Pin_20), J7.A21 (Pin_21), J7.A24 (Pin_24), J7.A25 (Pin_25)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
unnamed: D1.2 (A), R1.2
unnamed: J3.10, U1.2 (A1)
unnamed: J3.12, U1.3 (A2)
VAA: C1.1, J1.E39 (Pin_39), J1.F40 (Pin_40), J1.G39 (Pin_39), J1.H40 (Pin_40), J2.E39 (Pin_39), J2.F40 (Pin_40), J2.G39 (Pin_39), J2.H40 (Pin_40), J4.E39 (Pin_39), J4.F40 (Pin_40), J4.G39 (Pin_39), J4.H40 (Pin_40), J5.E39 (Pin_39), J5.F40 (Pin_40), J5.G39 (Pin_39), J5.H40 (Pin_40), J7.E39 (Pin_39), J7.F40 (Pin_40), J7.G39 (Pin_39), J7.H40 (Pin_40), J8.E39 (Pin_39), J8.F40 (Pin_40), J8.G39 (Pin_39), J8.H40 (Pin_40), U1.8 (VCCB)

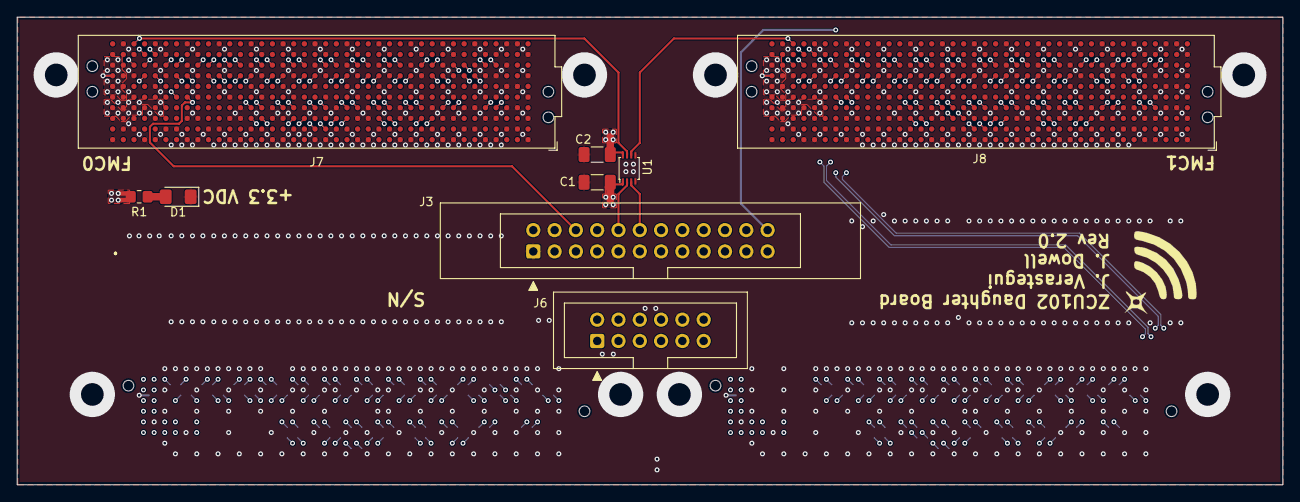
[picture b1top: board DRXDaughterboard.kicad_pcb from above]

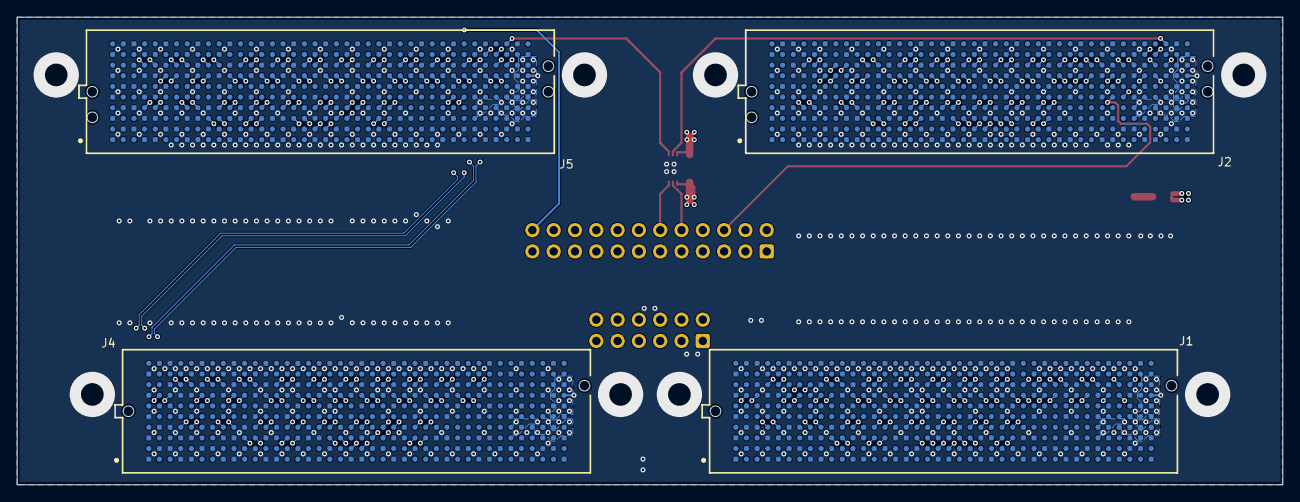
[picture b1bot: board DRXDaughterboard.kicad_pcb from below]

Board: 8 copper layers, 150.9 x 55.8 mm, 13 parts (4 on the bottom side), 164 nets.

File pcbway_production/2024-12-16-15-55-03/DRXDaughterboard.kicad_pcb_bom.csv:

Designator,Quantity,Value,Footprint,Package,MPN,Mount_Type
"C1, C2",2,100nF,C_1206_3216Metric_Pad1.33x1.80mm_HandSolder,1206,CL31B104KBCNFNC,smt
"J1, J2, J4, J5",4,Samtec_ASP-134488-01,ASP-134488-01,ASP-134488-01,ASP-134488-01,smt
J3,1,Conn_02x12_Odd_Even,IDC-Header_2x12_P2.54mm_Latch_Vertical,,302-S241,tht
J6,1,Conn_02x06_Odd_Even,IDC-Header_2x06_P2.54mm_Vertical,,BHR-12-VUA,tht
"J7, J8",2,Samtec_ASP-134486-01,Samtec_FMC_ASP-134486-01_10x40_P1.27mm_Vertical,,Do not populate,smt
U1,1,SN74LVC2T45DCUR,VSSOP-8_2.4x2.1mm_P0.5mm,8-VFSOP,SN74LVC2T45DCUR,smt

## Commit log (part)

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2025-02-11 It's KiCAD.
2025-10-08 cleanup.
2025-10-08 Add a README.md.
2025-10-22 KiCAD version update and serial number area on front silkscreen.
